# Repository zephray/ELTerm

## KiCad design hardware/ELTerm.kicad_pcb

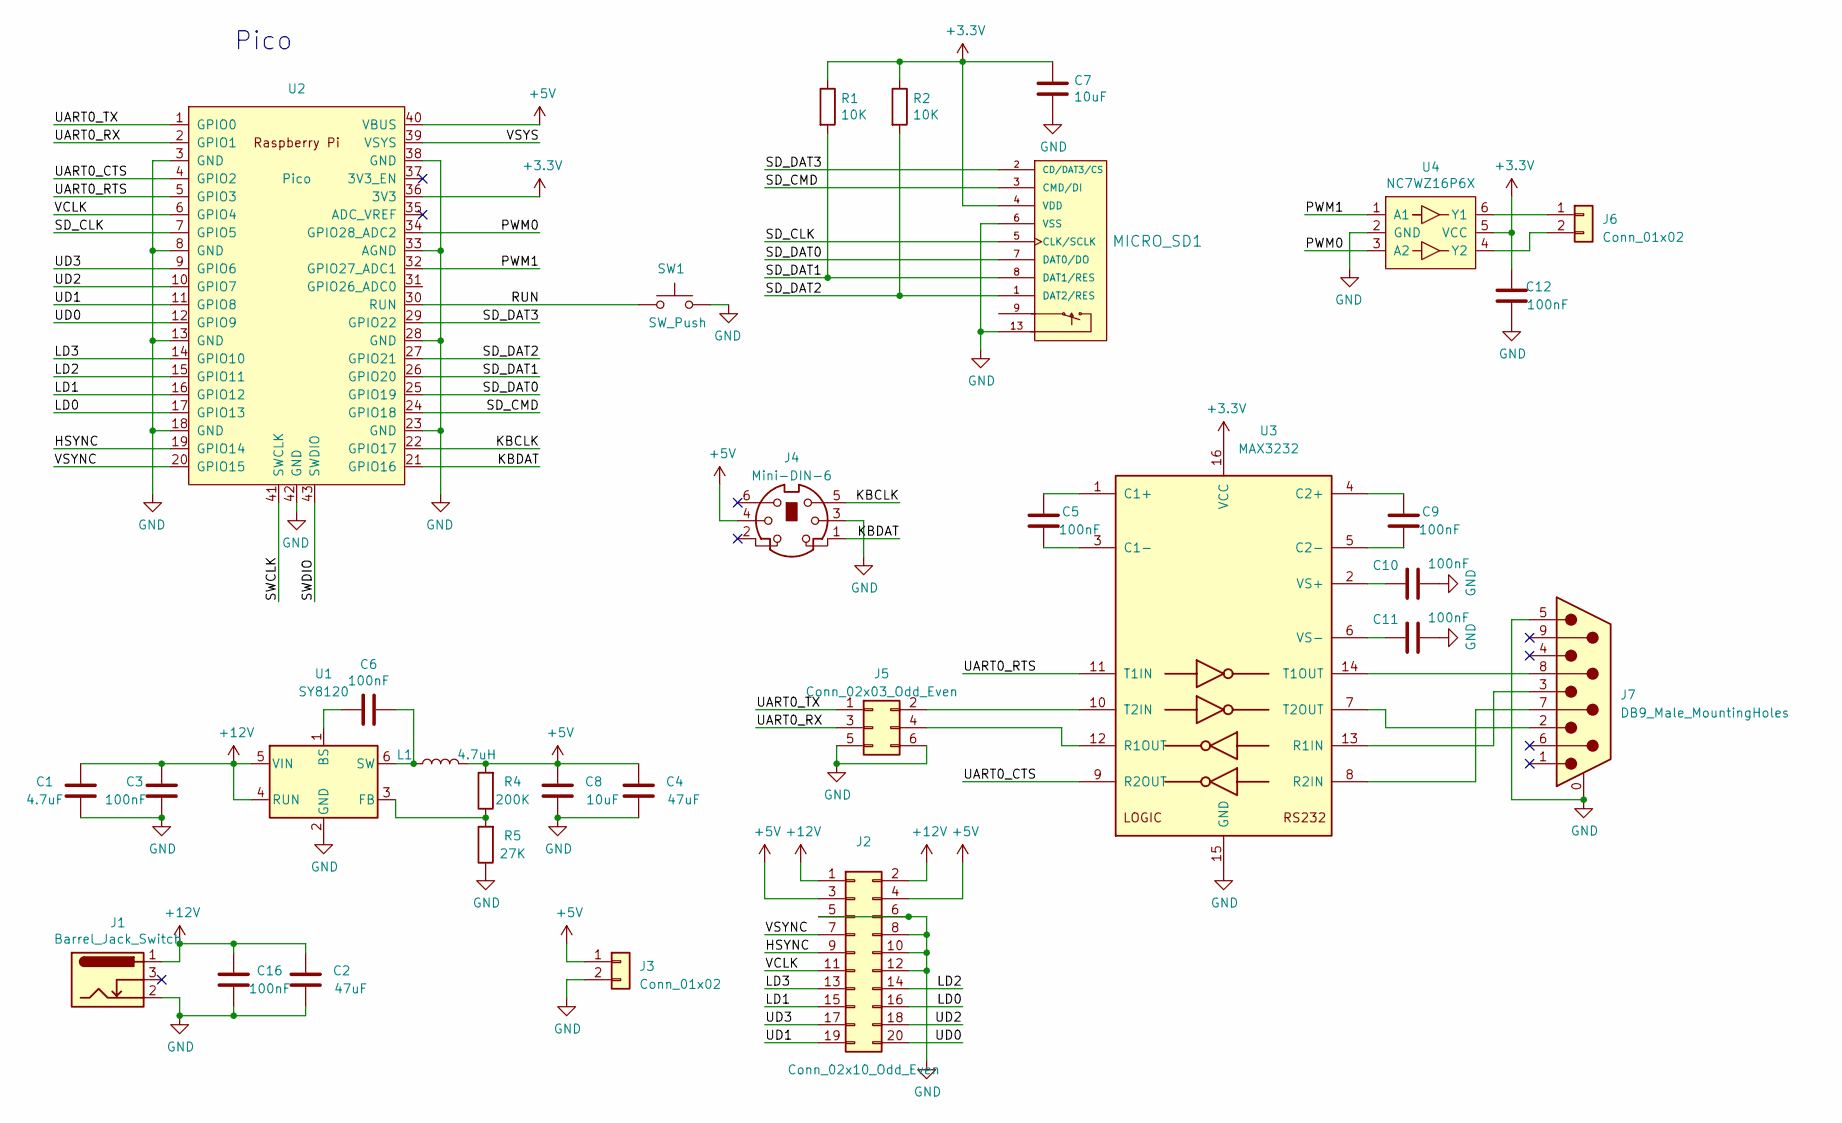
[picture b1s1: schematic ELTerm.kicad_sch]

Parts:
C1: 4.7uF; C_0805_2012Metric
C2, C4: 47uF; C_Elec_5x5.8
C3, C5, C6, C9, C10, C11, C12, C16: 100nF; C_0603_1608Metric
C7, C8: 10uF; C_0603_1608Metric
J1: Barrel_Jack_Switch; BarrelJack_Horizontal
J2: Conn_02x10_Odd_Even; PinHeader_2x10_P2.00mm_Vertical
J3, J6: Conn_01x02; PinHeader_1x02_P2.54mm_Vertical
J4: Mini-DIN-6; MINI-DIN-6-FULL-SHIELD
J5: Conn_02x03_Odd_Even; PinHeader_2x03_P2.54mm_Vertical
J7: DB9_Male_MountingHoles; DSUB-9_Male_Horizontal_P2.77x2.84mm_EdgePinOffset4.94mm_Hou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
L1: 4.7uH; L_Vishay_IHLP-1212
MICRO_SD1: MICRO_SD(TFC-WPAPR-08); TFC-WPAPR-08
R1, R2: 10K; R_0603_1608Metric
R4: 200K; R_0603_1608Metric
R5: 27K; R_0603_1608Metric
SW1: SW_Push; SW_SPST_CK_RS282G05A3
U1: SY8120; TSOT-23-6
U2: Pico; RPi_Pico_SMD_TH
U3: MAX3232; SO-16_3.9x9.9mm_P1.27mm
U4: NC7WZ16P6X; SOT-363_SC-70-6

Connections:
+3V3: C7.1, C12.2, MICRO_SD1.4 (VDD), R1.1, R2.1, U2.36 (3V3), U3.16 (VCC), U4.5 (VCC)
+5V: C4.2, C8.2, J2.3, J2.4, J3.1, J4.4, L1.2, R4.2, U2.40 (VBUS)
+12V: C1.2, C2.2, C3.2, C16.2, J1.1, J2.1, J2.2, U1.4 (RUN), U1.5 (VIN)
/HSYNC: J2.9, U2.19 (GPIO14)
/KBCLK: J4.5, U2.22 (GPIO17)
/KBDAT: J4.1, U2.21 (GPIO16)
/LD0: J2.16, U2.17 (GPIO13)
/LD1: J2.15, U2.16 (GPIO12)
/LD2: J2.14, U2.15 (GPIO11)
/LD3: J2.13, U2.14 (GPIO10)
/PWM0: U2.34 (GPIO28_ADC2), U4.3 (A2)
/PWM1: U2.32 (GPIO27_ADC1), U4.1 (A1)
/RUN: SW1.1, U2.30 (RUN)
/SD_CLK: MICRO_SD1.5 (CLK/SCLK), U2.7 (GPIO5)
/SD_CMD: MICRO_SD1.3 (CMD/DI), U2.24 (GPIO18)
/SD_DAT0: MICRO_SD1.7 (DAT0/DO), U2.25 (GPIO19)
/SD_DAT1: MICRO_SD1.8 (DAT1/RES), R1.2, U2.26 (GPIO20)
/SD_DAT2: MICRO_SD1.1 (DAT2/RES), R2.2, U2.27 (GPIO21)
/SD_DAT3: MICRO_SD1.2 (CD/DAT3/CS), U2.29 (GPIO22)
/SWCLK: U2.41 (SWCLK)
/SWDIO: U2.43 (SWDIO)
/UART0_CTS: U2.4 (GPIO2), U3.9 (R2OUT)
/UART0_RTS: U2.5 (GPIO3), U3.11 (T1IN)
/UART0_RX: J5.3, U2.2 (GPIO1)
/UART0_TX: J5.1, U2.1 (GPIO0)
/UD0: J2.20, U2.12 (GPIO9)
/UD1: J2.19, U2.11 (GPIO8)
/UD2: J2.18, U2.10 (GPIO7)
/UD3: J2.17, U2.9 (GPIO6)
/VCLK: J2.11, U2.6 (GPIO4)
/VSYNC: J2.7, U2.20 (GPIO15)
/VSYS: U2.39 (VSYS)
GND: C1.1, C2.1, C3.1, C4.1, C7.2, C8.1, C10.1, C11.1, C12.1, C16.1, J1.2, J2.5, J2.6, J2.8, J2.10, J2.12, J3.2, J4.3, J5.5, J5.6, J7.0 (PAD), J7.5, MICRO_SD1.6 (VSS), MICRO_SD1.10, MICRO_SD1.11, MICRO_SD1.12, MICRO_SD1.13, R5.1, SW1.2, U1.2 (GND), U2.3 (GND), U2.8 (GND), U2.13 (GND), U2.18 (GND), U2.23 (GND), U2.28 (GND), U2.33 (AGND), U2.38 (GND), U2.42 (GND), U3.15 (GND), U4.2 (GND)
unnamed: C5.1, U3.3 (C1-)
unnamed: C5.2, U3.1 (C1+)
unnamed: C6.1, L1.1, U1.6 (SW)
unnamed: C6.2, U1.1 (BS)
unnamed: C9.1, U3.5 (C2-)
unnamed: C9.2, U3.4 (C2+)
unnamed: C10.2, U3.2 (VS+)
unnamed: C11.2, U3.6 (VS-)
unnamed: J5.2, U3.10 (T2IN)
unnamed: J5.4, U3.12 (R1OUT)
unnamed: J6.1, U4.6 (Y1)
unnamed: J6.2, U4.4 (Y2)
unnamed: J7.2, U3.7 (T2OUT)
unnamed: J7.3, U3.13 (R1IN)
unnamed: J7.7, U3.8 (R2IN)
unnamed: J7.8, U3.14 (T1OUT)
unnamed: R4.1, R5.2, U1.3 (FB)

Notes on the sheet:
Pico

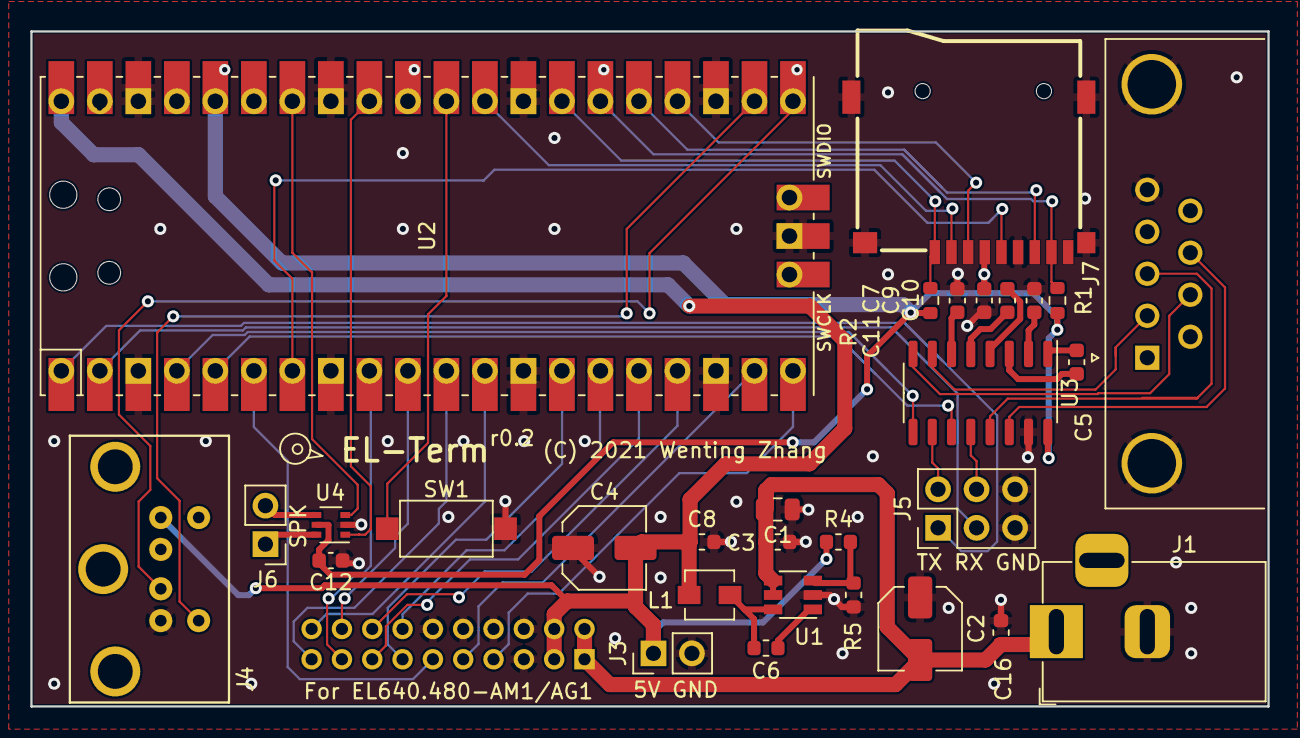
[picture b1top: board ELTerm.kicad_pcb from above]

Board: 2 copper layers, 81.6 x 44.5 mm, 31 parts (1 on the bottom side), 47 nets.

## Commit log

2021-03-24 - initial firmware with serial RX and EL display
2021-03-24 - Add license file in the root directory (source code already has license header)
2021-03-25 - Implement scrolling, optimize grahpics performance
2021-03-25 - License header formatting change
2021-03-26 - Support USB keyboard; Move UART; Handle more escape sequences
2021-03-28 - Support more vt/xterm features
2021-04-09 adapt to r0.1 hardware
2021-04-10 - Initial unit test support
2021-04-10 - Add supported feature list
2021-04-11 - Add more tests, fix various sequence handling bugs
2021-04-11 - PCB r0.2
2022-01-07 - Fix PCB EL pin assignment
2022-03-01 - Update to work with r0.2 PCB - Update to compile with new tinyUSB library - General fixes
2022-03-23 - Break terminal main into init and loop - Fix cursor handling
2022-03-23 - Provide PC emulator

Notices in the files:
hardware/ELTerm.kicad_pcb:
(C) 2021 Wenting Zhang
